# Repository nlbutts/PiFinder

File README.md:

# PiFinder
A VL53L0x board for the Raspberry PI

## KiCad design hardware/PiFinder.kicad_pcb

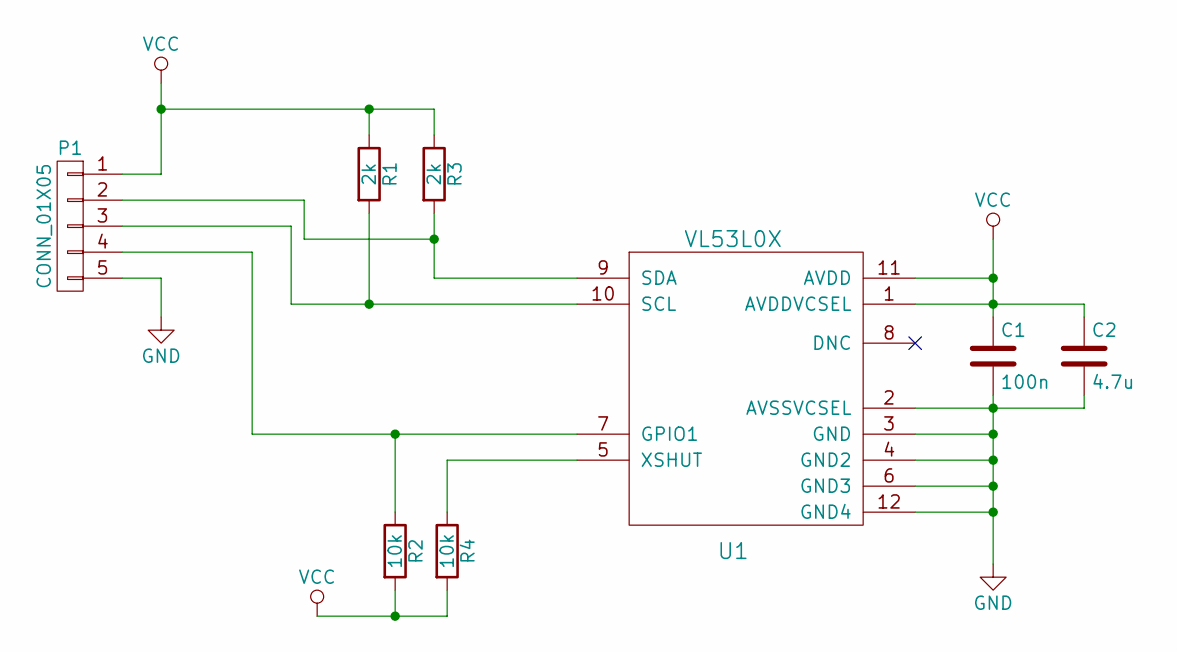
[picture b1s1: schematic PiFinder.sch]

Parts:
C1: 100n; C_0805; PartNum CL21B104MBCNNNC
C2: 4.7u; C_0805; PartNum CL21A475KQFNNNG
P1: CONN_01X05; Pin_Header_Straight_1x05
R1, R3: 2k; R_0805; PartNum MCR10ERTJ432
R2, R4: 10k; R_0805; PartNum MCR10FZPJ103
U1: VL53L0X; VL53L0x; PartNum VL53L0CXV0DH/1

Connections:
GND: C1.2, C2.2, P1.5, U1.2 (AVSSVCSEL), U1.3 (GND), U1.4 (GND2), U1.6 (GND3), U1.12 (GND4)
unnamed: P1.2, R3.2, U1.9 (SDA)
unnamed: P1.3, R1.2, U1.10 (SCL)
unnamed: P1.4, R2.1, U1.7 (GPIO1)
unnamed: R4.1, U1.5 (XSHUT)
VCC: C1.1, C2.1, P1.1, R1.1, R2.2, R3.1, R4.2, U1.1 (AVDDVCSEL), U1.11 (AVDD)

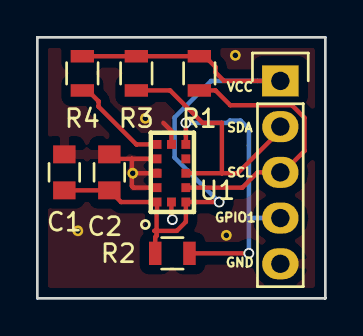
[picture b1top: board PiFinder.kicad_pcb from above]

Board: 2 copper layers, 16.0 x 14.5 mm, 8 parts (0 on the bottom side), 6 nets.

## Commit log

2016-11-27 Initial checkin.
2016-11-27 Finalized the design. Ready to order.
2016-12-09 Order the PCB.
2017-01-03 Added the VL53L0x user manual
2017-01-04 Updated some of the silk screen.
2017-01-05 Updated the part numbers.
2017-01-22 Added the software for the Raspberry Pi
2019-06-17 Trying to get python bindings working.
2019-06-27 Checked in the start of the PiFinder app.
2019-06-27 Refactored things.
2019-06-28 Refactored build system to utilize Python setuptools to call CMake.

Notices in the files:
hardware/PiFinder.kicad_pcb:
Copyright 2017
